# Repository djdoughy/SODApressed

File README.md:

# SODApressed
Percussive Enveloping Noise Generator

Features:

 -555 driven envelope

 -Triggerable by almost anything, at any length+

   -Attack cannot be retriggered until decay starts (this can make for some interesting half time hits if trigger is faster than attack time)

 -Transistor Noise generator

 -Beginner style DIY build

 -It's mostly analog!

Notes on building:
If you want a longer attack and decay, swap the capacitor on C5 from 4.7uF to 10uF (16V or larger)! Experiment! Have Fun!

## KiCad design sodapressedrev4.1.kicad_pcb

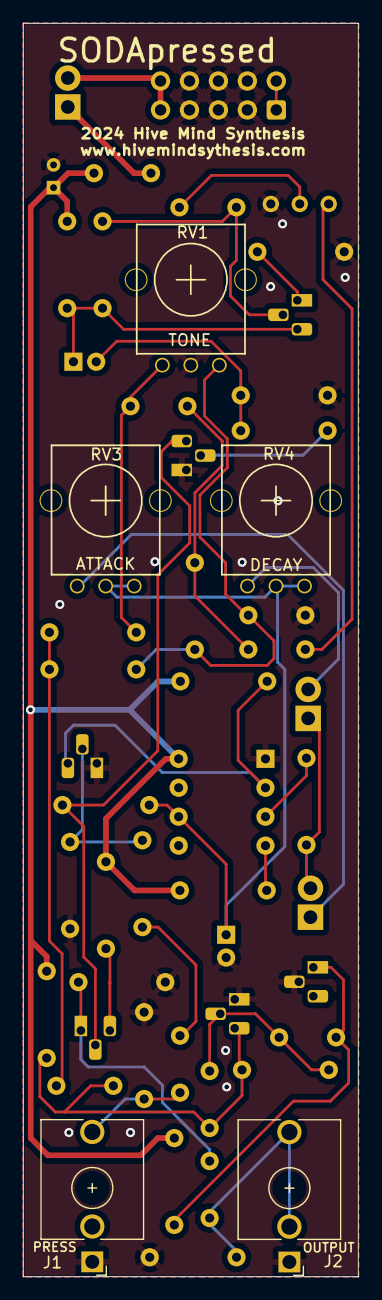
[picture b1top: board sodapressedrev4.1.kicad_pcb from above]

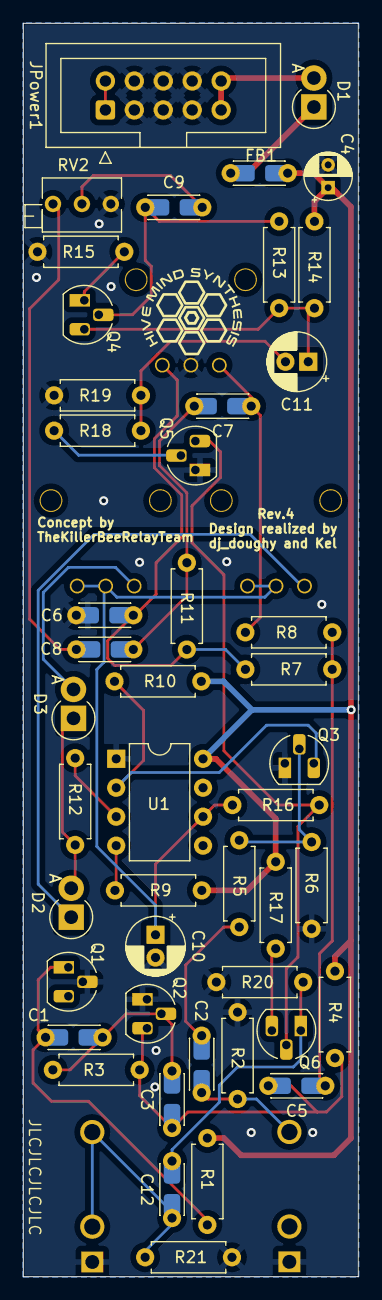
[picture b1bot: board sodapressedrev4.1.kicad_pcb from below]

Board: 2 copper layers, 29.4 x 110.0 mm, 51 parts (46 on the bottom side), 33 nets.

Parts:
C1: .1uF; C_Disc_P5.00mm_0805
C2: 1nF; C_Disc_P5.00mm_0805
C3: 10p; C_Disc_P5.00mm_0805
C4: 10u; CP_Radial_D4.0mm_P2.00mm
C5, C8: 1uF; C_Disc_P5.00mm_0805
C6, C7: 27nF; C_Disc_P5.00mm_0805
C9, C12: 10uF; C_Disc_P5.00mm_0805
C10: 4.7uF; CP_Radial_D5.0mm_P2.00mm
C11: 1uF; CP_Radial_D5.0mm_P2.00mm
D1: 1N5819; D_DO-15_P2.54mm_Vertical_AnodeUp
D2, D3: 1N4148; D_DO-15_P2.54mm_Vertical_AnodeUp
FB1: FerriteBead_Small; C_Disc_P5.00mm_0805
J1: PRESS; Jack_3.5mm_QingPu_WQP-PJ398SM_Vertical_CircularHoles
J2: Output; Jack_3.5mm_QingPu_WQP-PJ398SM_Vertical_CircularHoles
JPower1: EurorackPower; IDC-Header_2x05_P2.54mm_Vertical
Q1, Q2, Q3, Q4, Q5, Q6: 2N3904; TO-92_HandSolder
R1: 200k; R_Axial_DIN0207_L6.3mm_D2.5mm_P7.62mm_Horizontal
R2, R5, R10: 10k; R_Axial_DIN0207_L6.3mm_D2.5mm_P7.62mm_Horizontal
R3: 2M2; R_Axial_DIN0207_L6.3mm_D2.5mm_P7.62mm_Horizontal
R4, R7, R8, R11, R19, R20, R21: 4k7; R_Axial_DIN0207_L6.3mm_D2.5mm_P7.62mm_Horizontal
R6, R9, R18: 100k; R_Axial_DIN0207_L6.3mm_D2.5mm_P7.62mm_Horizontal
R12: 1k; R_Axial_DIN0207_L6.3mm_D2.5mm_P7.62mm_Horizontal
R13: 1M; R_Axial_DIN0207_L6.3mm_D2.5mm_P7.62mm_Horizontal
R14: 2.2k; R_Axial_DIN0207_L6.3mm_D2.5mm_P7.62mm_Horizontal
R15: 150; R_Axial_DIN0207_L6.3mm_D2.5mm_P7.62mm_Horizontal
R16: 110k; R_Axial_DIN0207_L6.3mm_D2.5mm_P7.62mm_Horizontal
R17: 100; R_Axial_DIN0207_L6.3mm_D2.5mm_P7.62mm_Horizontal
RV1: 10k; Alpha9mmPot
RV2: 100k; Potentiometer_Bourns_3266Z_Horizontal
RV3, RV4: 50k; Alpha9mmPot
U1: ICM7555xP; DIP-8_W7.62mm

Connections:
+12V: C4.1, FB1.2, R1.1, R4.1, R9.1, R10.1, R14.2, R17.2, U1.8 (VCC)
GND: C4.2, C6.2, C10.2, J1.S (Sleeve), J2.S (Sleeve), JPower1.3 (GND), JPower1.4 (GND), JPower1.5 (GND), JPower1.6 (GND), JPower1.7 (GND), JPower1.8 (GND), Q1.2 (B), Q2.1 (E), Q3.1 (E), Q5.1 (E), R2.2, R6.2, R15.1, R19.1, R20.1, R21.1, RV1.2, RV2.1, U1.1 (GND)
unnamed: C2.1, R5.1
unnamed: C5.1, R7.1, R8.2
unnamed: C6.1, R7.2, R11.1, RV1.3
unnamed: C7.1, R8.1, RV1.1
unnamed: C7.2, C8.2, R11.2
unnamed: C8.1, RV2.3
unnamed: C9.2, RV2.2
unnamed: C11.2, R18.2, R19.2
unnamed: D1.2 (A), JPower1.9 (+12V), JPower1.10 (+12V)
unnamed: D1.1 (K), FB1.1
unnamed: D2.2 (A), D3.1 (K), R12.2
unnamed: D2.1 (K), RV3.1
unnamed: D3.2 (A), RV4.1
unnamed: C2.2, J1.T (Tip), R2.1
unnamed: C12.1, J2.T (Tip), J2.TN (Tip_normalize), R21.2
unnamed: JPower1.1 (-12V), JPower1.2 (-12V)
unnamed: C1.2, Q1.1 (E), R1.2
unnamed: C1.1, C3.2, Q2.2 (B), R3.1
unnamed: C3.1, C5.2, Q2.3 (C), R3.2, R4.2
unnamed: Q3.2 (B), R5.2, R6.1
unnamed: Q3.3 (C), R10.2, U1.2 (TR)
unnamed: C9.1, Q4.2 (B), R13.1
unnamed: C11.1, Q4.3 (C), R13.2, R14.1
unnamed: Q4.1 (E), R15.2
unnamed: Q5.2 (B), R18.1
unnamed: Q5.3 (C), Q6.2 (B), R16.1
unnamed: Q6.3 (C), R17.1
unnamed: C12.2, Q6.1 (E), R20.2
unnamed: R12.1, U1.3 (Q)
unnamed: R9.2, U1.4 (R)
unnamed: C10.1, R16.2, RV3.2, RV3.3, RV4.2, RV4.3, U1.6 (THR)

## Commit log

2024-07-13 Init Project Upload
2024-07-13 iBOM upload
2024-07-13 Update README.md
    Feature info and image added
2024-07-13 Update README.md
    fixed typo
2024-07-13 Panel init
2024-07-16 Mouser BOM
    Importable mouser bom.
2024-07-16 Delete SodaPressed - MouserBom.xls
    Wrong parts
